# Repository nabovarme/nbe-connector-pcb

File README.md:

# nbe-connector-pcb
PCB for NBE main connector

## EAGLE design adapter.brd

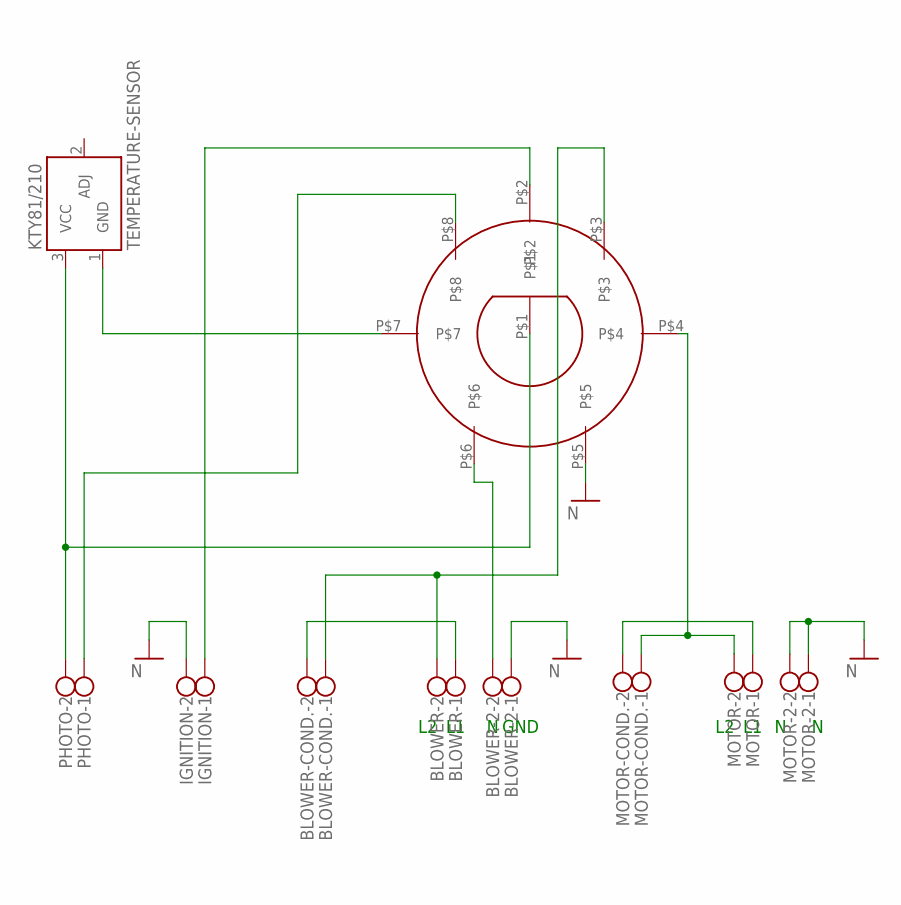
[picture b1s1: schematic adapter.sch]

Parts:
BLOWER: W237-102
BLOWER-2: W237-102
BLOWER-COND.: W237-102
IGNITION: W237-102
KTY81/210: TEMPERATURE-SENSOR; TO-92
MOTOR: W237-102
MOTOR-2: W237-102
MOTOR-COND.: W237-102
PHOTO: W237-102
U$1: PX0959/P

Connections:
GND: BLOWER-2.1, IGNITION.2, MOTOR-2.1, MOTOR-2.2, U$1.P$5
unnamed: PHOTO.1, U$1.P$8
unnamed: IGNITION.1, U$1.P$2
unnamed: KTY81/210.3 (VCC), PHOTO.2, U$1.P$1
unnamed: KTY81/210.1 (GND), U$1.P$7
unnamed: MOTOR.1, MOTOR-COND..2
unnamed: BLOWER.2, BLOWER-COND..1, U$1.P$3
unnamed: BLOWER-2.2, U$1.P$6
unnamed: BLOWER.1, BLOWER-COND..2
unnamed: MOTOR.2, MOTOR-COND..1, U$1.P$4

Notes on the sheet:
GND

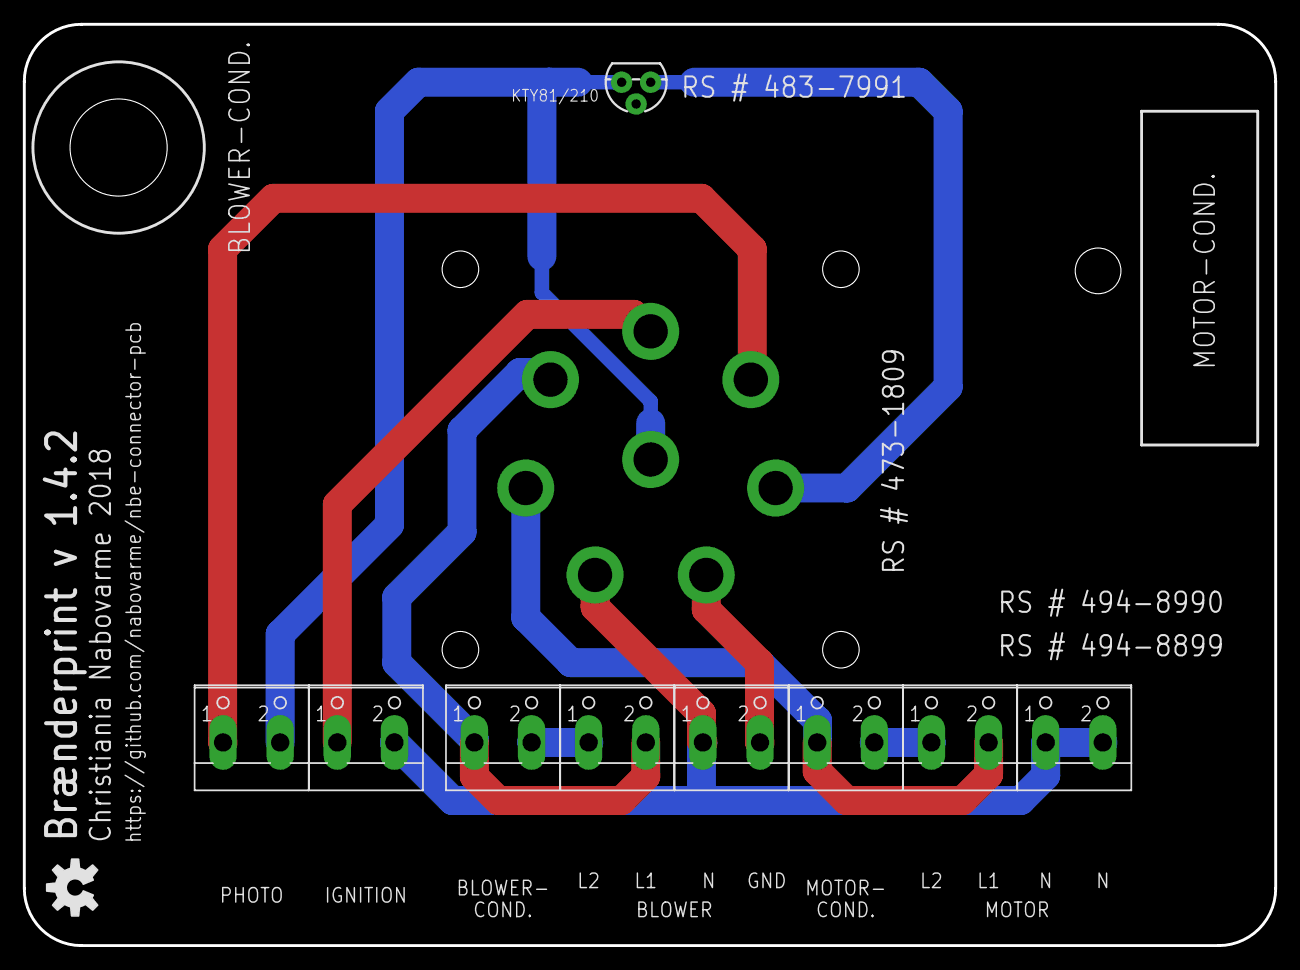
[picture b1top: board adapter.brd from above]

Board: 2 copper layers, 109.5 x 80.6 mm, 11 parts (1 on the bottom side), 10 nets.

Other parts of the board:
U$2: OSHW-LOGO-M

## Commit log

2018-03-26 initial version (v.1.3)
2018-03-26 new version (v.1.4)
    socket pin spacing changed from 5,02 mm to 5 mm
    grouped photo and ignition connectors
    added more silk info
    wider pcb with space for capacitor hole mount
2018-03-26 center aligned main connector on pcb
    version 1.4.1
2018-03-27 holes for screw terminals changed to 1.6 mm

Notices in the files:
parts and their libraries:
SparkFun-Sensors: Licensing: CC v3.0 Share-Alike You are welcome to use this library for commercial purposes.
